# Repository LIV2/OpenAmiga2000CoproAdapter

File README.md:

# OpenAmiga2000CoproAdapter

# A2000 Boss Experiment
This branch contains the code and pcb for a coprocessor containing a CPLD that allows host CPU takeover by doing proper bus arbitration
This doesn't completely work, E/VPA/VMA doesn't work properly causing CIA issues...

__I forgot to route DTACK to the CPLD, you will need to cut the DTACK trace, connect the socket's DTACK to TP1 and the Slot's DTACK to TP2__

## Theory of operation
This holds the coprocessor in a reset state until BOSS is asserted, doing so requires us to isolate some signals as the 68000 does not tristate them during DMA or HALT:

* Reset
* Halt
* RW
* LDS
* UDS
* AS
* BG
* BR
* FC0-2

Most of these are routed through the CPLD to acheive this except RESET/HALT which are bidirectional signals and necessitated a CBT buffer - but most if not all of these would be better served using a buffer rather than wasting CPLD resources

It is also necessary to generate an internal E clock (the 68k does not ever stop driving this) and generate VPA/DTACK around that to handle the CIA VPA/VMA stuff in a way that results in reliable operation. I still haven't figured this out yet...

OpenAmiga2000CoproAdapter is an Open Hardware adapter that allows installing the main processor of a Commodore Amiga 2000 computer in the co-processor slot.

### Summary
OpenAmiga2000CoproAdapter is an adapter that allows installing the main processor of a Commodore Amiga 2000 computer in the co-processor slot, based on [work by kipper2k](http://eab.abime.net/showthread.php?t=89604). It is mainly useful to mount TerribleFire and other accelerator cards without having to remove the floppy drive tray and without having them bump into your MegaChip, in case.

The adapter is very similar to the original, except that I skipped the INT7 and the A600 NMI circuits. Those are not needed for TerribleFire cards and for most other boards (I think they are for Vampires only). I carried over the INT2/OVR header, since the former is needed for the TF530. I have also introduced solder jumpers for the FR0-2 signals: those are not connected on kipper2k's board, I don't know why and it works well anyway, but I thought they wouldn't hurt as they will be open by default.

You may be able to install this without removing the original CPU by cutting the E jumper and closing the BOSS one.

This is a slightly expensive board to manufacture because it exceeds the 10x10cm limit that cheap fab houses impose, because it needs gold-plating for better contact and resistance to repeated insertions/removals, and because the edge connector should be beveled to ease insertion. These are the recommended settings if you want to get the boards made.

### Installation
**Please be very careful when plugging this board** in the co-processor slot: there is an arrow on the board, **it must point to the back of the Amiga**. Plugging this adapter backwards will damage your CPU/accelerator card, as some pins of the CPU slot carry +12V!

When this board is installed, most likely the original 68000 socket must be left empty unless you cut the E jumper and close the BOSS jumper, though this ultimately depends on the particular card you will be installing.

### License
The OpenAmiga2000CoproAdapter documentation, including the design itself, is copyright &copy; SukkoPera 2018-2019.

OpenAmiga2000CoproAdapter is Open Hardware licensed under the [CERN OHL v. 1.2](http://ohwr.org/cernohl).

You may redistribute and modify this documentation under the terms of the CERN OHL v.1.2. This documentation is distributed *as is* and WITHOUT ANY EXPRESS OR IMPLIED WARRANTIES whatsoever with respect to its functionality, operability or use, including, without limitation, any implied warranties OF MERCHANTABILITY, SATISFACTORY QUALITY, FITNESS FOR A PARTICULAR PURPOSE or infringement. We expressly disclaim any liability whatsoever for any direct, indirect, consequential, incidental or special damages, including, without limitation, lost revenues, lost profits, losses resulting from business interruption or loss of data, regardless of the form of action or legal theory under which the liability may be asserted, even if advised of the possibility or likelihood of such damages.

A copy of the full license is included in file [LICENSE.pdf](LICENSE.pdf), please refer to it for applicable conditions. In order to properly deal with its terms, please see file [LICENSE_HOWTO.pdf](LICENSE_HOWTO.pdf).

The contact points for information about manufactured Products (see section 4.2) are listed in file [PRODUCT.md](PRODUCT.md).

Any modifications made by Licensees (see section 3.4.b) shall be recorded in file [CHANGES.md](CHANGES.md).

The Documentation Location of the original project is https://github.com/SukkoPera/OpenAmiga2000CoproAdapter/.

### Support the Project
Since the project is open you are free to get the PCBs made by your preferred manufacturer, however in case you want to support the development, you can order them from PCBWay through this link:

You get cheap, professionally-made and good quality PCBs, I get some credit that will help with this and [other projects](https://www.pcbway.com/project/member/shareproject/?bmbid=41100). You won't even have to worry about the various PCB options, it's all pre-configured for you!

Also, if you still have to register to that site, [you can use this link](https://www.pcbway.com/setinvite.aspx?inviteid=41100) to get some bonus initial credit (and yield me some more).

Again, if you want to use another manufacturer, feel free to, don't feel obligated :). But then you can buy me a coffee if you want:

### Get Help
If you need help or have questions, you can join [the official Telegram group](https://t.me/joinchat/HUHdWBC9J9JnYIrvTYfZmg).

### Thanks
Thanks to kipper2k, of course :).

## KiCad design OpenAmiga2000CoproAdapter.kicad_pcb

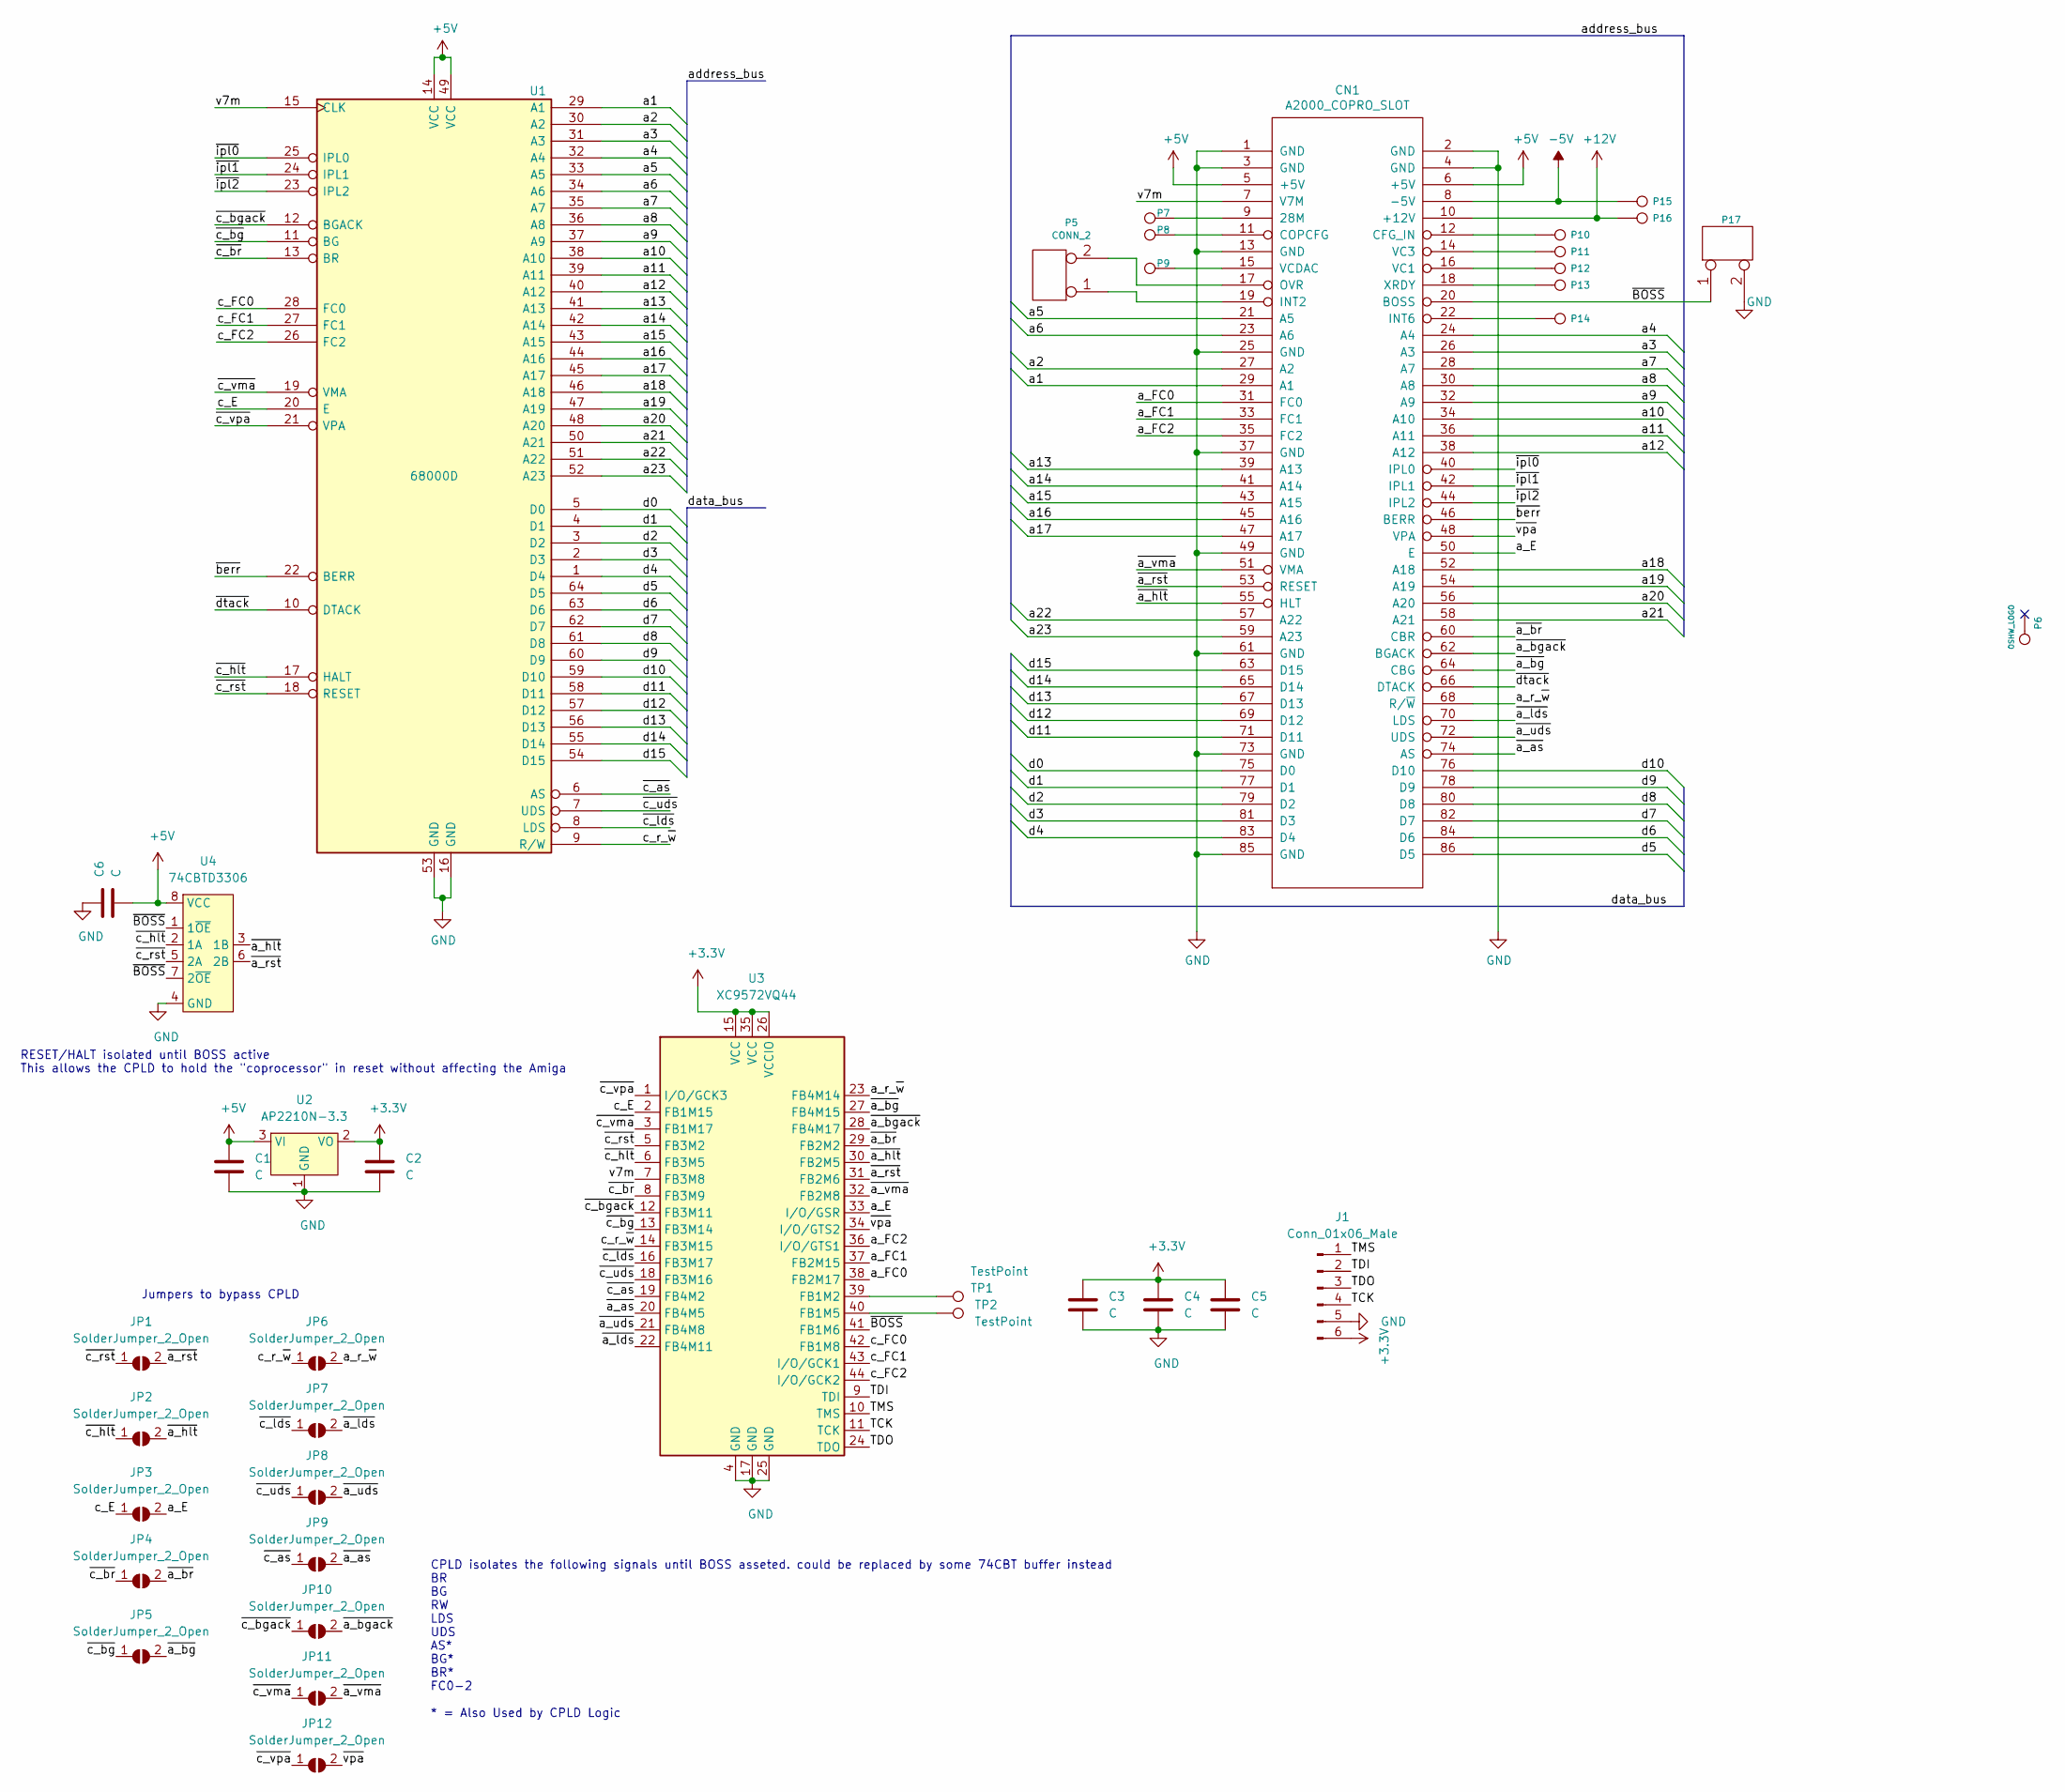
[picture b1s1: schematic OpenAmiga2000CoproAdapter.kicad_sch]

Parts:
C1, C2, C3, C4, C5, C6: C; C_0603_1608Metric_Pad1.08x0.95mm_HandSolder
CN1: A2000_COPRO_SLOT
J1: Conn_01x06_Male; PinHeader_1x06_P2.54mm_Vertical
JP1, JP2, JP3, JP4, JP5, JP6, JP7, JP8, JP9, JP10, JP11, JP12: SolderJumper_2_Open; SolderJumper-2_P1.3mm_Open_TrianglePad1.0x1.5mm
P5: CONN_2; PinHeader_1x02_P2.54mm_Vertical
P6: OSHW_LOGO; OSHW-Logo_7.5x8mm_Copper
P7, P8, P9, P10, P11, P12, P13, P14, P15, P16: CONN_1; TestPoint_Pad_D1.5mm
P17: CONN_2; SolderJumper-2_P1.3mm_Open_RoundedPad1.0x1.5mm
TP1, TP2: TestPoint; TestPoint_Pad_D1.0mm
U1: 68000D; DIP-64_W22.86mm_Socket_LongPads
U2: AP2210N-3.3; SOT-23_Handsoldering
U3: XC9572VQ44; TQFP-44_10x10mm_P0.8mm
U4: 74CBTD3306; SOIC-8_3.9x4.9mm_P1.27mm

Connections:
+3V3: C2.1, C3.1, C4.1, C5.1, J1.6, U2.2 (VO), U3.15 (VCC), U3.26 (VCCIO), U3.35 (VCC)
+5V: C1.1, C6.2, CN1.5 (+5V), CN1.6 (+5V), U1.14 (VCC), U1.49 (VCC), U2.3 (VI), U4.8 (VCC)
+12V: CN1.10 (+12V), P16.1
-5V: CN1.8 (-5V), P15.1
/TCK: J1.4, U3.11 (TCK)
/TDI: J1.2, U3.9 (TDI)
/TDO: J1.3, U3.24 (TDO)
/TMS: J1.1, U3.10 (TMS)
/a1: CN1.29 (A1), U1.29 (A1)
/a2: CN1.27 (A2), U1.30 (A2)
/a3: CN1.26 (A3), U1.31 (A3)
/a4: CN1.24 (A4), U1.32 (A4)
/a5: CN1.21 (A5), U1.33 (A5)
/a6: CN1.23 (A6), U1.34 (A6)
/a7: CN1.28 (A7), U1.35 (A7)
/a8: CN1.30 (A8), U1.36 (A8)
/a9: CN1.32 (A9), U1.37 (A9)
/a10: CN1.34 (A10), U1.38 (A10)
/a11: CN1.36 (A11), U1.39 (A11)
/a12: CN1.38 (A12), U1.40 (A12)
/a13: CN1.39 (A13), U1.41 (A13)
/a14: CN1.41 (A14), U1.42 (A14)
/a15: CN1.43 (A15), U1.43 (A15)
/a16: CN1.45 (A16), U1.44 (A16)
/a17: CN1.47 (A17), U1.45 (A17)
/a18: CN1.52 (A18), U1.46 (A18)
/a19: CN1.54 (A19), U1.47 (A19)
/a20: CN1.56 (A20), U1.48 (A20)
/a21: CN1.58 (A21), U1.50 (A21)
/a22: CN1.57 (A22), U1.51 (A22)
/a23: CN1.59 (A23), U1.52 (A23)
/a_E: CN1.50 (E), JP3.2 (B), U3.33 (I/O/GSR)
/a_FC0: CN1.31 (FC0), U3.38 (FB2M17)
/a_FC1: CN1.33 (FC1), U3.37 (FB2M15)
/a_FC2: CN1.35 (FC2), U3.36 (I/O/GTS1)
/a_r_~w: CN1.68 (R/~W), JP6.2 (B), U3.23 (FB4M14)
/c_E: JP3.1 (A), U1.20 (E), U3.2 (FB1M15)
/c_FC0: U1.28 (FC0), U3.42 (FB1M8)
/c_FC1: U1.27 (FC1), U3.43 (I/O/GCK1)
/c_FC2: U1.26 (FC2), U3.44 (I/O/GCK2)
/c_r_~w: JP6.1 (A), U1.9 (R/W), U3.14 (FB3M15)
/d0: CN1.75 (D0), U1.5 (D0)
/d1: CN1.77 (D1), U1.4 (D1)
/d2: CN1.79 (D2), U1.3 (D2)
/d3: CN1.81 (D3), U1.2 (D3)
/d4: CN1.83 (D4), U1.1 (D4)
/d5: CN1.86 (D5), U1.64 (D5)
/d6: CN1.84 (D6), U1.63 (D6)
/d7: CN1.82 (D7), U1.62 (D7)
/d8: CN1.80 (D8), U1.61 (D8)
/d9: CN1.78 (D9), U1.60 (D9)
/d10: CN1.76 (D10), U1.59 (D10)
/d11: CN1.71 (D11), U1.58 (D11)
/d12: CN1.69 (D12), U1.57 (D12)
/d13: CN1.67 (D13), U1.56 (D13)
/d14: CN1.65 (D14), U1.55 (D14)
/d15: CN1.63 (D15), U1.54 (D15)
/v7m: CN1.7 (V7M), U1.15 (CLK), U3.7 (FB3M8)
/~BOSS: CN1.20 (BOSS), P17.1, U3.41 (FB1M6), U4.1 (1~OE), U4.7 (2~OE)
/~a_as: CN1.74 (AS), JP9.2 (B), U3.20 (FB4M5)
/~a_bg: CN1.64 (CBG), JP5.2 (B), U3.27 (FB4M15)
/~a_bgack: CN1.62 (BGACK), JP10.2 (B), U3.28 (FB4M17)
/~a_br: CN1.60 (CBR), JP4.2 (B), U3.29 (FB2M2)
/~a_hlt: CN1.55 (HLT), JP2.2 (B), U3.30 (FB2M5), U4.3 (1B)
/~a_lds: CN1.70 (LDS), JP7.2 (B), U3.22 (FB4M11)
/~a_rst: CN1.53 (RESET), JP1.2 (B), U3.31 (FB2M6), U4.6 (2B)
/~a_uds: CN1.72 (UDS), JP8.2 (B), U3.21 (FB4M8)
/~a_vma: CN1.51 (VMA), JP11.2 (B), U3.32 (FB2M8)
/~berr: CN1.46 (BERR), U1.22 (BERR)
/~c_as: JP9.1 (A), U1.6 (AS), U3.19 (FB4M2)
/~c_bg: JP5.1 (A), U1.11 (BG), U3.13 (FB3M14)
/~c_bgack: JP10.1 (A), U1.12 (BGACK), U3.12 (FB3M11)
/~c_br: JP4.1 (A), U1.13 (BR), U3.8 (FB3M9)
/~c_hlt: JP2.1 (A), U1.17 (HALT), U3.6 (FB3M5), U4.2 (1A)
/~c_lds: JP7.1 (A), U1.8 (LDS), U3.16 (FB3M17)
/~c_rst: JP1.1 (A), U1.18 (RESET), U3.5 (FB3M2), U4.5 (2A)
/~c_uds: JP8.1 (A), U1.7 (UDS), U3.18 (FB3M16)
/~c_vma: JP11.1 (A), U1.19 (VMA), U3.3 (FB1M17)
/~c_vpa: JP12.1 (A), U1.21 (VPA), U3.1 (I/O/GCK3)
/~dtack: CN1.66 (DTACK), U1.10 (DTACK)
/~ipl0: CN1.40 (IPL0), U1.25 (IPL0)
/~ipl1: CN1.42 (IPL1), U1.24 (IPL1)
/~ipl2: CN1.44 (IPL2), U1.23 (IPL2)
/~vpa: CN1.48 (VPA), JP12.2 (B), U3.34 (I/O/GTS2)
GND: C1.2, C2.2, C3.2, C4.2, C5.2, C6.1, CN1.1 (GND), CN1.2 (GND), CN1.3 (GND), CN1.4 (GND), CN1.13 (GND), CN1.25 (GND), CN1.37 (GND), CN1.49 (GND), CN1.61 (GND), CN1.73 (GND), CN1.85 (GND), J1.5, P17.2 (PM), U1.16 (GND), U1.53 (GND), U2.1 (GND), U3.4 (GND), U3.17 (GND), U3.25 (GND), U4.4 (GND)
unnamed: CN1.9 (28M), P7.1
unnamed: CN1.11 (COPCFG), P8.1
unnamed: CN1.12 (CFG_IN), P10.1
unnamed: CN1.14 (VC3), P11.1
unnamed: CN1.15 (VCDAC), P9.1
unnamed: CN1.16 (VC1), P12.1
unnamed: CN1.17 (OVR), P5.2 (PM)
unnamed: CN1.18 (XRDY), P13.1
unnamed: CN1.19 (INT2), P5.1
unnamed: CN1.22 (INT6), P14.1
unnamed: TP1.1, U3.39 (FB1M2)
unnamed: TP2.1, U3.40 (FB1M5)

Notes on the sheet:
RESET/HALT isolated until BOSS active This allows the CPLD to hold the "coprocessor" in reset without affecting the Amiga
Jumpers to bypass CPLD
CPLD isolates the following signals until BOSS asseted. could be replaced by some 74CBT buffer instead BR BG RW LDS UDS AS* BG* BR* FC0-2 * = Also Used by CPLD Logic

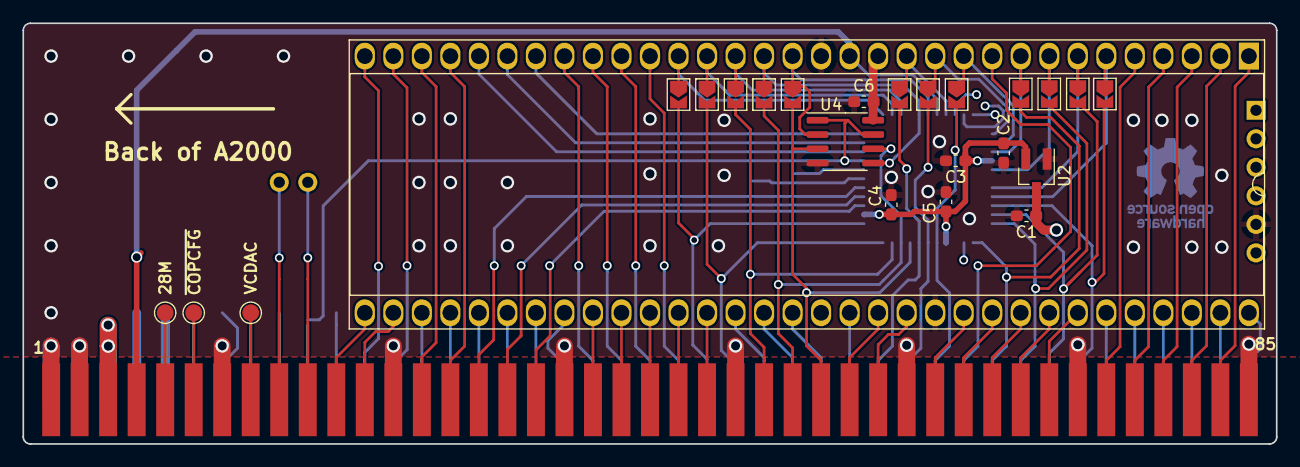
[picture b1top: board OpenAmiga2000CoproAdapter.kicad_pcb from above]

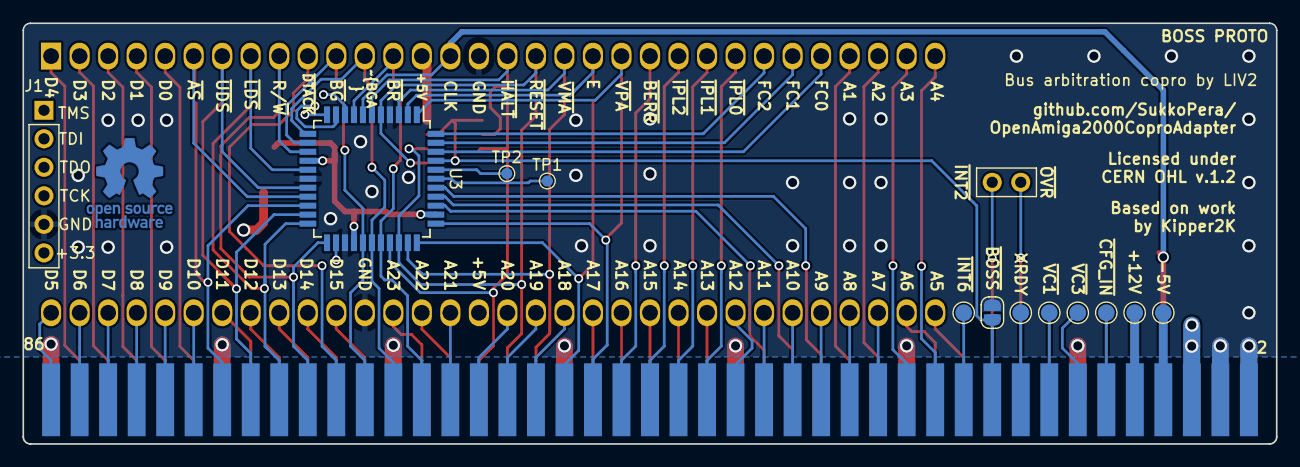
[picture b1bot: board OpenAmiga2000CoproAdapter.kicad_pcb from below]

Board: 4 copper layers, 111.6 x 37.5 mm, 39 parts (14 on the bottom side), 97 nets.

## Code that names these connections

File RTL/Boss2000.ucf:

#PACE: Start of Constraints generated by PACE

#PACE: Start of PACE I/O Pin Assignments
NET "a_AS"  LOC = "P20"  ; 
NET "a_BG"  LOC = "P27"  ; 
NET "a_BGACK"  LOC = "P28"  ; 
NET "a_BR"  LOC = "P29"  ; 
NET "a_DTACK"  LOC = "P40"  ;
NET "a_E"  LOC = "P33"  ; 
NET "a_FC0"  LOC = "P38"  ; 
NET "a_FC1"  LOC = "P37"  ; 
NET "a_FC2"  LOC = "P36"  ; 
NET "a_HALT"  LOC = "P30"  ; 
NET "a_LDS"  LOC = "P22"  ; 
NET "a_RESET"  LOC = "P31"  ; 
NET "a_RW"  LOC = "P23"  ; 
NET "a_UDS"  LOC = "P21"  ; 
NET "a_VMA"  LOC = "P32"  ; 
NET "BOSSn"  LOC = "P41"  ; 
NET "c_AS"  LOC = "P19"  ; 
NET "c_BG"  LOC = "P13"  ; 
NET "c_BGACK"  LOC = "P12"  ; 
NET "c_BR"  LOC = "P8"  ; 
NET "c_E"  LOC = "P2"  ; 
NET "c_FC0"  LOC = "P42"  ; 
NET "c_FC1"  LOC = "P43"  ; 
NET "c_FC2"  LOC = "P44"  ; 
NET "c_HALT"  LOC = "P6"  ; 
NET "c_LDS"  LOC = "P16"  ; 
NET "c_RESET"  LOC = "P5"  ; 
NET "c_RW"  LOC = "P14"  ; 
NET "c_UDS"  LOC = "P18"  ; 
NET "c_VMA"  LOC = "P3"  ; 
NET "C_VPA"  LOC = "P1"  ; 
NET "CLK"  LOC = "P7"  ; 
NET "DTACK"  LOC = "P39"  ; 
NET "VPA"  LOC = "P34"  ; 

#PACE: Start of PACE Area Constraints

#PACE: Start of PACE Prohibit Constraints

#PACE: End of Constraints generated by PACE

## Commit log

2021-02-03 Experiment arbitrating bus away from mainboard cpu
2021-05-30 Add CPLD to test out boss functionality
2021-06-28 Boss proto stuff

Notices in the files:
OpenAmiga2000CoproAdapter.kicad_pcb:
Licensed under CERN OHL v.1.2
